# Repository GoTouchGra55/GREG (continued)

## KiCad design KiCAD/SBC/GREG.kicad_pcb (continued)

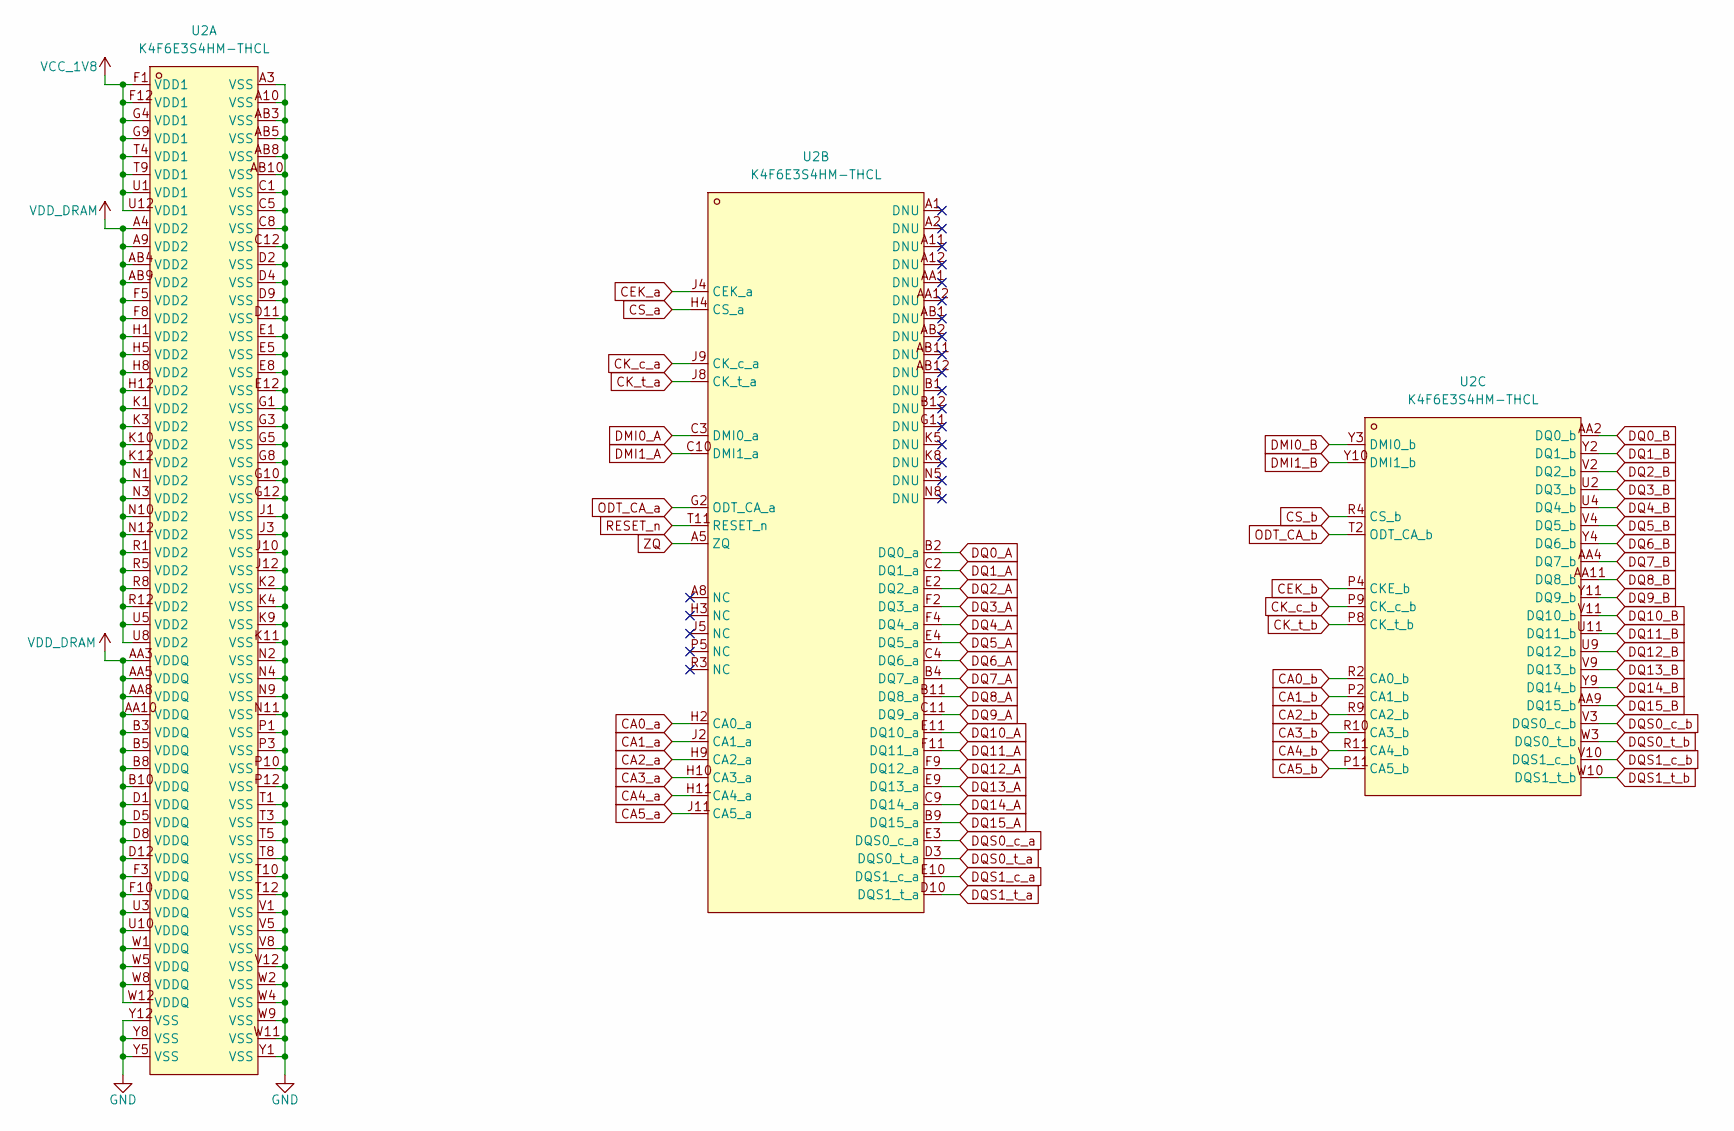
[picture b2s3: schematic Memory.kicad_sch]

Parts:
U2: K4F6E3S4HM-THCL; FBGA-200_L15.0-W10.0-BL_K4F6E3S4HM; MPN K4F6E3S4HM-THCL; LCSC Part C2920224

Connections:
CA0_a: U2.H2 (CA0_a); also elsewhere on the board
CA0_b: U2.R2 (CA0_b); also elsewhere on the board
CA1_a: U2.J2 (CA1_a); also elsewhere on the board
CA1_b: U2.P2 (CA1_b); also elsewhere on the board
CA2_a: U2.H9 (CA2_a); also elsewhere on the board
CA2_b: U2.R9 (CA2_b); also elsewhere on the board
CA3_a: U2.H10 (CA3_a); also elsewhere on the board
CA3_b: U2.R10 (CA3_b); also elsewhere on the board
CA4_a: U2.H11 (CA4_a); also elsewhere on the board
CA4_b: U2.R11 (CA4_b); also elsewhere on the board
CA5_a: U2.J11 (CA5_a); also elsewhere on the board
CA5_b: U2.P11 (CA5_b); also elsewhere on the board
CEK_a: U2.J4 (CEK_a), U2.P4 (CKE_b); also elsewhere on the board
CK_c_a: U2.J9 (CK_c_a), U2.P9 (CK_c_b); also elsewhere on the board
CK_t_a: U2.J8 (CK_t_a), U2.P8 (CK_t_b); also elsewhere on the board
CS_a: U2.H4 (CS_a); also elsewhere on the board
CS_b: U2.R4 (CS_b); also elsewhere on the board
DMI0_A: U2.C3 (DMI0_a); also elsewhere on the board
DMI0_B: U2.Y3 (DMI0_b); also elsewhere on the board
DMI1_A: U2.C10 (DMI1_a); also elsewhere on the board
DMI1_B: U2.Y10 (DMI1_b); also elsewhere on the board
DQ0_A: U2.B2 (DQ0_a); also elsewhere on the board
DQ0_B: U2.AA2 (DQ0_b); also elsewhere on the board
DQ1_A: U2.C2 (DQ1_a); also elsewhere on the board
DQ1_B: U2.Y2 (DQ1_b); also elsewhere on the board
DQ2_A: U2.E2 (DQ2_a); also elsewhere on the board
DQ2_B: U2.V2 (DQ2_b); also elsewhere on the board
DQ3_A: U2.F2 (DQ3_a); also elsewhere on the board
DQ3_B: U2.U2 (DQ3_b); also elsewhere on the board
DQ4_A: U2.F4 (DQ4_a); also elsewhere on the board
DQ4_B: U2.U4 (DQ4_b); also elsewhere on the board
DQ5_A: U2.E4 (DQ5_a); also elsewhere on the board
DQ5_B: U2.V4 (DQ5_b); also elsewhere on the board
DQ6_A: U2.C4 (DQ6_a); also elsewhere on the board
DQ6_B: U2.Y4 (DQ6_b); also elsewhere on the board
DQ7_A: U2.B4 (DQ7_a); also elsewhere on the board
DQ7_B: U2.AA4 (DQ7_b); also elsewhere on the board
DQ8_A: U2.B11 (DQ8_a); also elsewhere on the board
DQ8_B: U2.AA11 (DQ8_b); also elsewhere on the board
DQ9_A: U2.C11 (DQ9_a); also elsewhere on the board
DQ9_B: U2.Y11 (DQ9_b); also elsewhere on the board
DQ10_A: U2.E11 (DQ10_a); also elsewhere on the board
DQ10_B: U2.V11 (DQ10_b); also elsewhere on the board
DQ11_A: U2.F11 (DQ11_a); also elsewhere on the board
DQ11_B: U2.U11 (DQ11_b); also elsewhere on the board
DQ12_A: U2.F9 (DQ12_a); also elsewhere on the board
DQ12_B: U2.U9 (DQ12_b); also elsewhere on the board
DQ13_A: U2.E9 (DQ13_a); also elsewhere on the board
DQ13_B: U2.V9 (DQ13_b); also elsewhere on the board
DQ14_A: U2.C9 (DQ14_a); also elsewhere on the board
DQ14_B: U2.Y9 (DQ14_b); also elsewhere on the board
DQ15_A: U2.B9 (DQ15_a); also elsewhere on the board
DQ15_B: U2.AA9 (DQ15_b); also elsewhere on the board
DQS0_c_a: U2.E3 (DQS0_c_a); also elsewhere on the board
DQS0_c_b: U2.V3 (DQS0_c_b)
DQS0_t_a: U2.D3 (DQS0_t_a); also elsewhere on the board
DQS0_t_b: U2.W3 (DQS0_t_b)
DQS1_c_a: U2.E10 (DQS1_c_a); also elsewhere on the board
DQS1_c_b: U2.V10 (DQS1_c_b)
DQS1_t_a: U2.D10 (DQS1_t_a); also elsewhere on the board
DQS1_t_b: U2.W10 (DQS1_t_b)
GND: U2.A3 (VSS), U2.A10 (VSS), U2.AB3 (VSS), U2.AB5 (VSS), U2.AB8 (VSS), U2.AB10 (VSS), U2.C1 (VSS), U2.C5 (VSS), U2.C8 (VSS), U2.C12 (VSS), U2.D2 (VSS), U2.D4 (VSS), U2.D9 (VSS), U2.D11 (VSS), U2.E1 (VSS), U2.E5 (VSS), U2.E8 (VSS), U2.E12 (VSS), U2.G1 (VSS), U2.G3 (VSS), U2.G5 (VSS), U2.G8 (VSS), U2.G10 (VSS), U2.G12 (VSS), U2.J1 (VSS), U2.J3 (VSS), U2.J10 (VSS), U2.J12 (VSS), U2.K2 (VSS), U2.K4 (VSS), U2.K9 (VSS), U2.K11 (VSS), U2.N2 (VSS), U2.N4 (VSS), U2.N9 (VSS), U2.N11 (VSS), U2.P1 (VSS), U2.P3 (VSS), U2.P10 (VSS), U2.P12 (VSS), U2.T1 (VSS), U2.T3 (VSS), U2.T5 (VSS), U2.T8 (VSS), U2.T10 (VSS), U2.T12 (VSS), U2.V1 (VSS), U2.V5 (VSS), U2.V8 (VSS), U2.V12 (VSS), U2.W2 (VSS), U2.W4 (VSS), U2.W9 (VSS), U2.W11 (VSS), U2.Y1 (VSS), U2.Y5 (VSS), U2.Y8 (VSS), U2.Y12 (VSS); also elsewhere on the board
ODT_CA_a: U2.G2 (ODT_CA_a); also elsewhere on the board
ODT_CA_b: U2.T2 (ODT_CA_b); also elsewhere on the board
RESET_n: U2.T11 (RESET_n); also elsewhere on the board
VCC_1V8: U2.F1 (VDD1), U2.F12 (VDD1), U2.G4 (VDD1), U2.G9 (VDD1), U2.T4 (VDD1), U2.T9 (VDD1), U2.U1 (VDD1), U2.U12 (VDD1); also elsewhere on the board
VDD_DRAM: U2.A4 (VDD2), U2.A9 (VDD2), U2.AA3 (VDDQ), U2.AA5 (VDDQ), U2.AA8 (VDDQ), U2.AA10 (VDDQ), U2.AB4 (VDD2), U2.AB9 (VDD2), U2.B3 (VDDQ), U2.B5 (VDDQ), U2.B8 (VDDQ), U2.B10 (VDDQ), U2.D1 (VDDQ), U2.D5 (VDDQ), U2.D8 (VDDQ), U2.D12 (VDDQ), U2.F3 (VDDQ), U2.F5 (VDD2), U2.F8 (VDD2), U2.F10 (VDDQ), U2.H1 (VDD2), U2.H5 (VDD2), U2.H8 (VDD2), U2.H12 (VDD2), U2.K1 (VDD2), U2.K3 (VDD2), U2.K10 (VDD2), U2.K12 (VDD2), U2.N1 (VDD2), U2.N3 (VDD2), U2.N10 (VDD2), U2.N12 (VDD2), U2.R1 (VDD2), U2.R5 (VDD2), U2.R8 (VDD2), U2.R12 (VDD2), U2.U3 (VDDQ), U2.U5 (VDD2), U2.U8 (VDD2), U2.U10 (VDDQ), U2.W1 (VDDQ), U2.W5 (VDDQ), U2.W8 (VDDQ), U2.W12 (VDDQ); also elsewhere on the board
ZQ: U2.A5 (ZQ); also elsewhere on the board

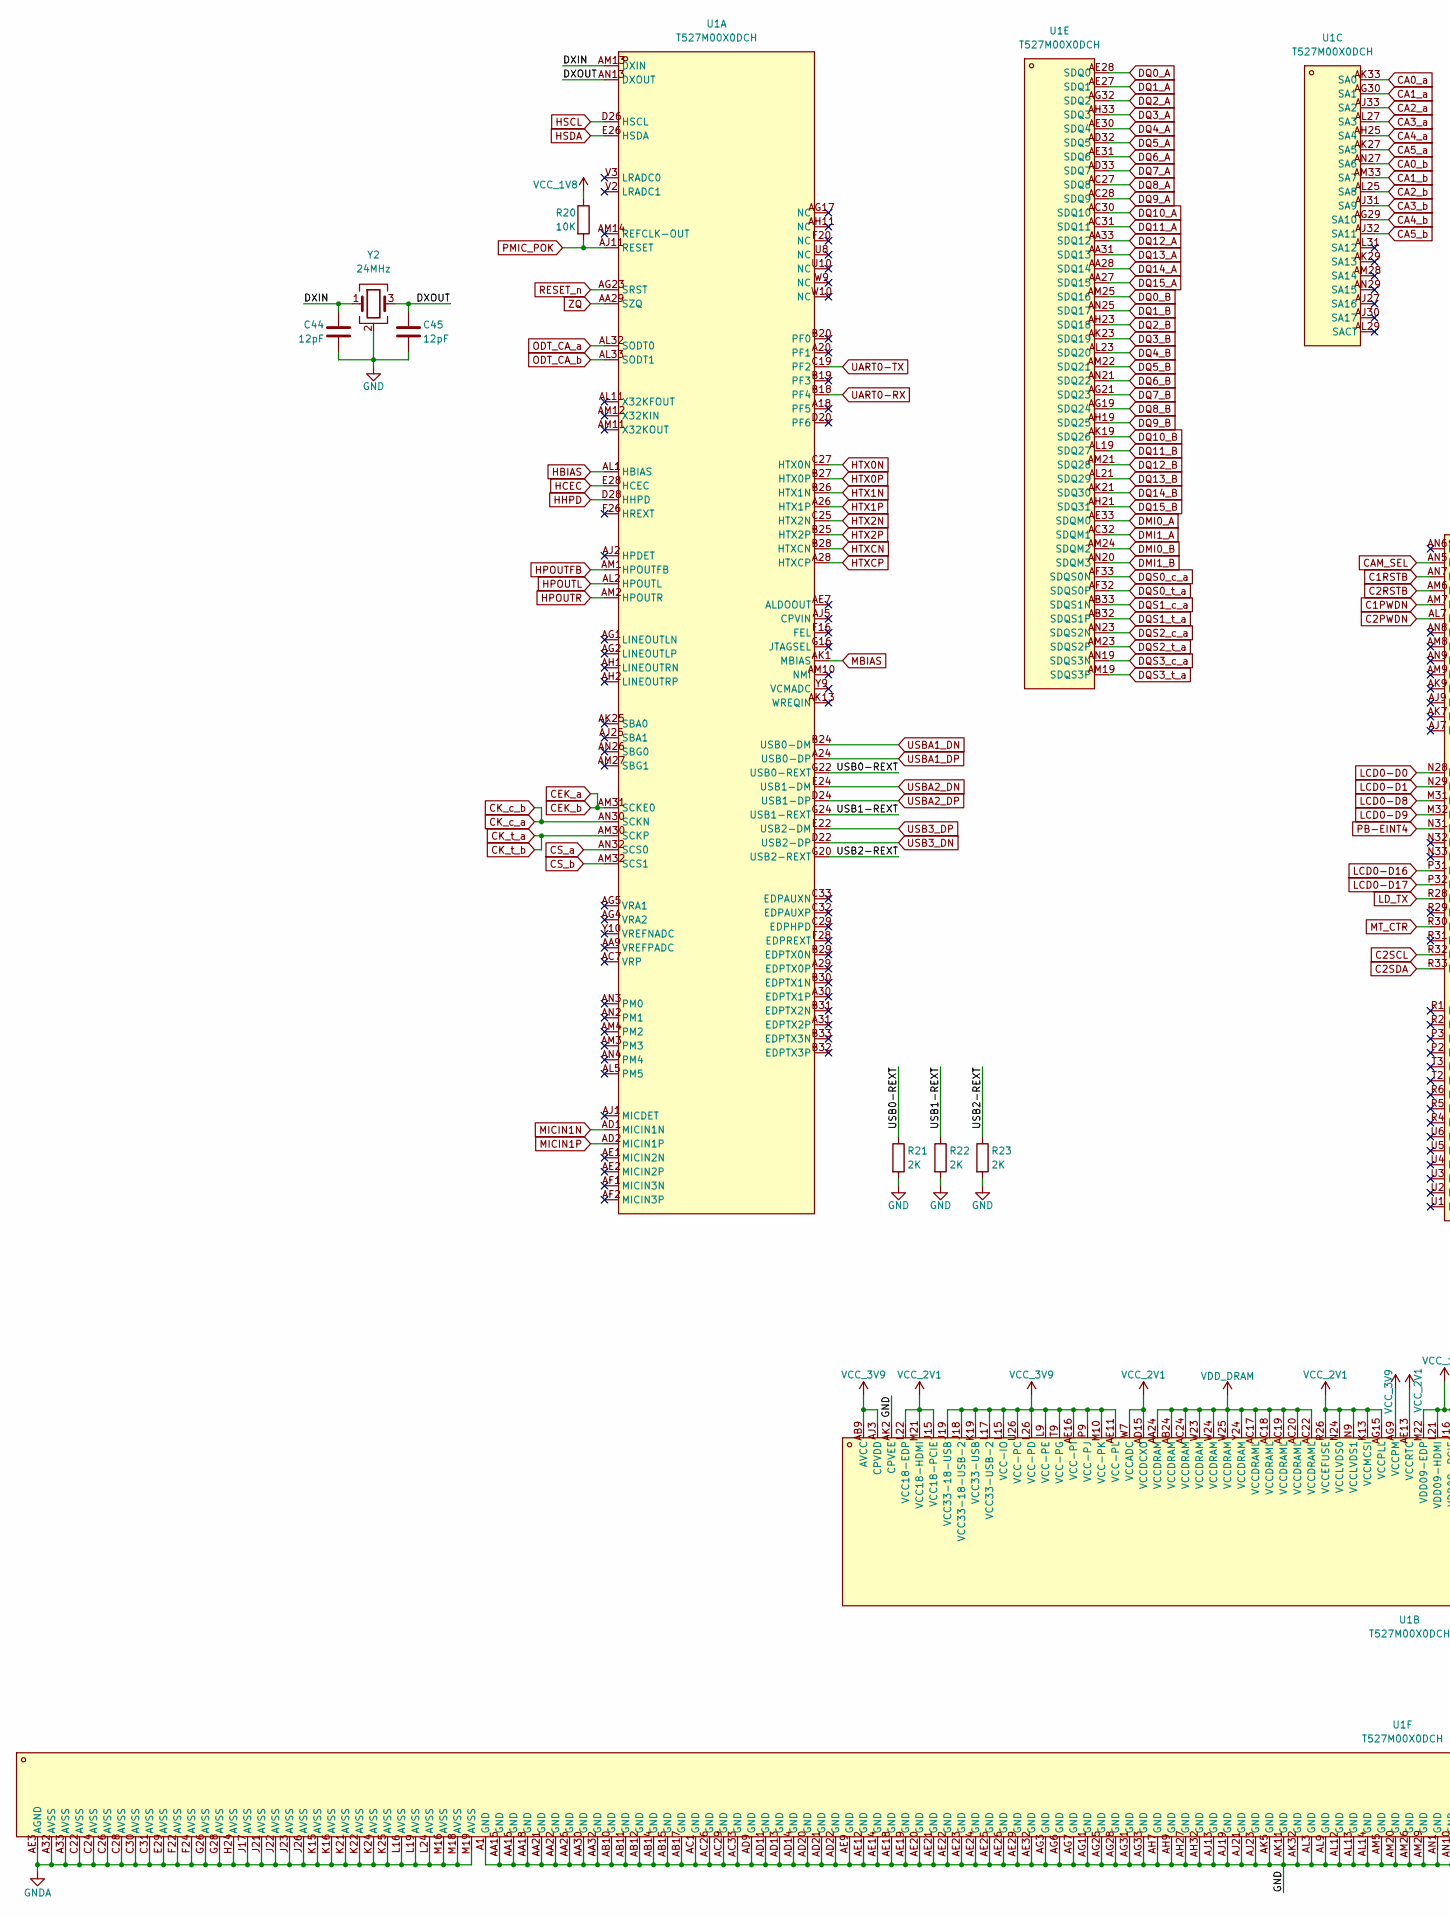
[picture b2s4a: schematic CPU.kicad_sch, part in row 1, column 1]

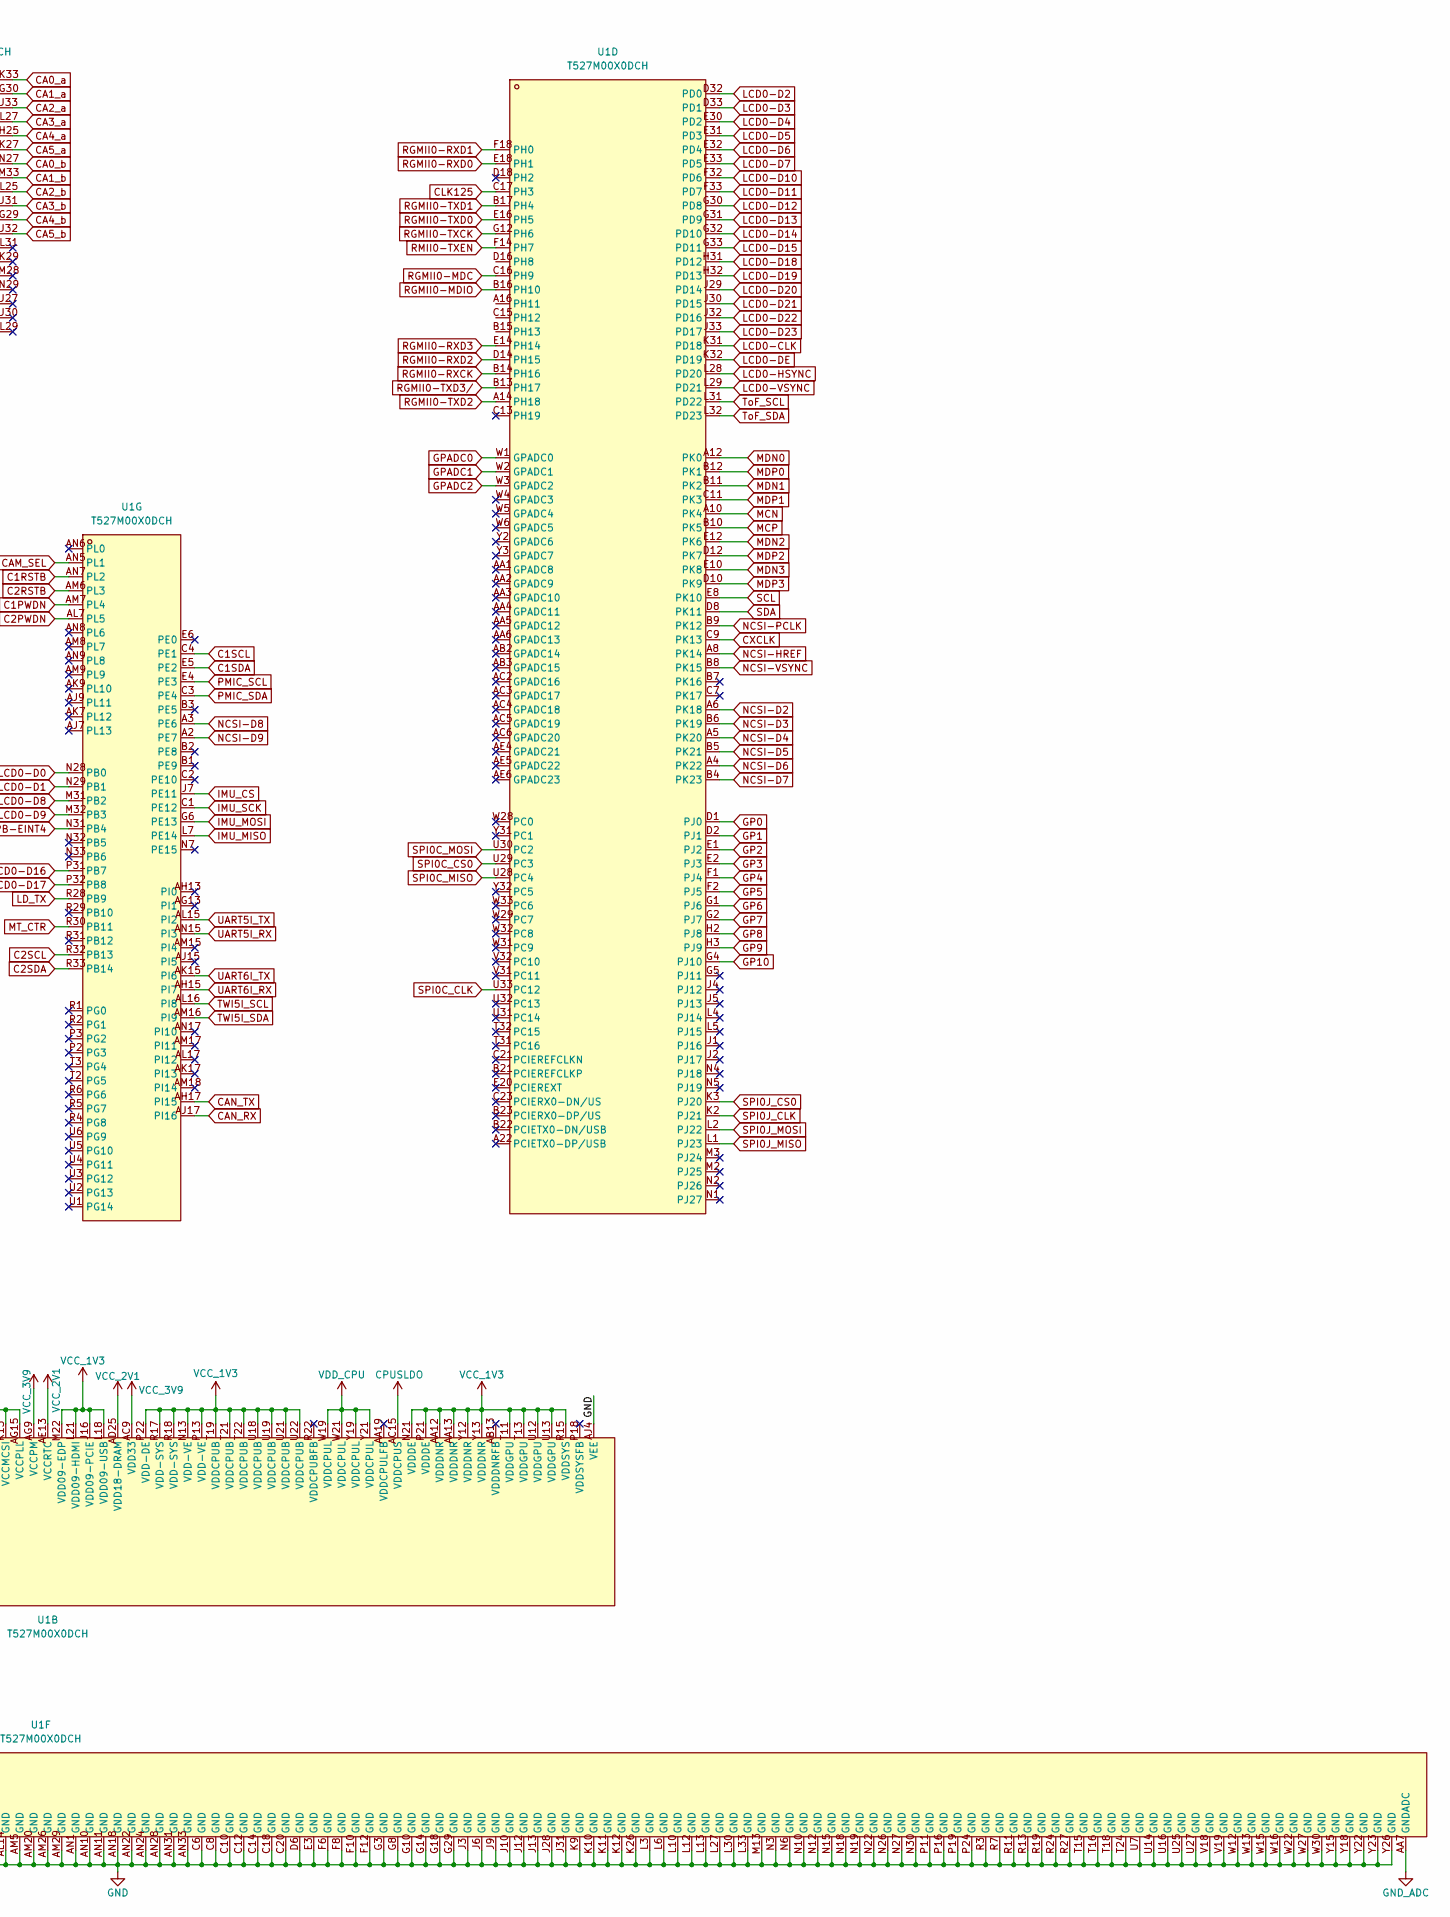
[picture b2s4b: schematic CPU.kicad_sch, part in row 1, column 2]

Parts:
C44, C45: 12pF; C_0402_1005Metric
R20: 10K; R_0402_1005Metric
R21, R22, R23: 2K; R_0402_1005Metric
U1: T527M00X0DCH; BGA-664_L17.0-W17.0_T527; MPN T527M00X0DCH; LCSC Part C28310420
Y2: 24MHz; Crystal_SMD_3225-4Pin_3.2x2.5mm

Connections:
/CPU/DXIN: C44.1, U1.AM13 (DXIN), Y2.1
/CPU/DXOUT: C45.1, U1.AN13 (DXOUT), Y2.3
/CPU/USB0-REXT: R21.1, U1.G22 (USB0-REXT)
/CPU/USB1-REXT: R22.1, U1.G24 (USB1-REXT)
/CPU/USB2-REXT: R23.1, U1.G20 (USB2-REXT)
C1PWDN: U1.AM7 (PL4); also elsewhere on the board
C1RSTB: U1.AN7 (PL2); also elsewhere on the board
C1SCL: U1.C4 (PE1); also elsewhere on the board
C1SDA: U1.E5 (PE2); also elsewhere on the board
C2PWDN: U1.AL7 (PL5); also elsewhere on the board
C2RSTB: U1.AM6 (PL3); also elsewhere on the board
C2SCL: U1.R32 (PB13); also elsewhere on the board
C2SDA: U1.R33 (PB14); also elsewhere on the board
CA0_a: U1.AK33 (SA0); also elsewhere on the board
CA0_b: U1.AN27 (SA6); also elsewhere on the board
CA1_a: U1.AG30 (SA1); also elsewhere on the board
CA1_b: U1.AM33 (SA7); also elsewhere on the board
CA2_a: U1.AJ33 (SA2); also elsewhere on the board
CA2_b: U1.AL25 (SA8); also elsewhere on the board
CA3_a: U1.AL27 (SA3); also elsewhere on the board
CA3_b: U1.AJ31 (SA9); also elsewhere on the board
CA4_a: U1.AH25 (SA4); also elsewhere on the board
CA4_b: U1.AG29 (SA10); also elsewhere on the board
CA5_a: U1.AK27 (SA5); also elsewhere on the board
CA5_b: U1.AJ32 (SA11); also elsewhere on the board
CAM_SEL: U1.AN5 (PL1); also elsewhere on the board
CAN_RX: U1.AJ17 (PI16); also elsewhere on the board
CAN_TX: U1.AH17 (PI15); also elsewhere on the board
CEK_a: U1.AM31 (SCKE0); also elsewhere on the board
CK_c_a: U1.AN30 (SCKN); also elsewhere on the board
CK_t_a: U1.AM30 (SCKP); also elsewhere on the board
CLK125: U1.C17 (PH3); also elsewhere on the board
CPUSLDO: U1.AC15 (VDDCPUS); also elsewhere on the board
CS_a: U1.AN32 (SCS0); also elsewhere on the board
CS_b: U1.AM32 (SCS1); also elsewhere on the board
CXCLK: U1.C9 (PK13); also elsewhere on the board
DMI0_A: U1.AE33 (SDQM0); also elsewhere on the board
DMI0_B: U1.AM24 (SDQM2); also elsewhere on the board
DMI1_A: U1.AC32 (SDQM1); also elsewhere on the board
DMI1_B: U1.AN20 (SDQM3); also elsewhere on the board
DQ0_A: U1.AE28 (SDQ0); also elsewhere on the board
DQ0_B: U1.AM25 (SDQ16); also elsewhere on the board
DQ1_A: U1.AE27 (SDQ1); also elsewhere on the board
DQ1_B: U1.AN25 (SDQ17); also elsewhere on the board
DQ2_A: U1.AG32 (SDQ2); also elsewhere on the board
DQ2_B: U1.AH23 (SDQ18); also elsewhere on the board
DQ3_A: U1.AH33 (SDQ3); also elsewhere on the board
DQ3_B: U1.AK23 (SDQ19); also elsewhere on the board
DQ4_A: U1.AE30 (SDQ4); also elsewhere on the board
DQ4_B: U1.AL23 (SDQ20); also elsewhere on the board
DQ5_A: U1.AD32 (SDQ5); also elsewhere on the board
DQ5_B: U1.AM22 (SDQ21); also elsewhere on the board
DQ6_A: U1.AE31 (SDQ6); also elsewhere on the board
DQ6_B: U1.AN21 (SDQ22); also elsewhere on the board
DQ7_A: U1.AD33 (SDQ7); also elsewhere on the board
DQ7_B: U1.AG21 (SDQ23); also elsewhere on the board
DQ8_A: U1.AC27 (SDQ8); also elsewhere on the board
DQ8_B: U1.AG19 (SDQ24); also elsewhere on the board
DQ9_A: U1.AC28 (SDQ9); also elsewhere on the board
DQ9_B: U1.AH19 (SDQ25); also elsewhere on the board
DQ10_A: U1.AC30 (SDQ10); also elsewhere on the board
DQ10_B: U1.AK19 (SDQ26); also elsewhere on the board
DQ11_A: U1.AC31 (SDQ11); also elsewhere on the board
DQ11_B: U1.AL19 (SDQ27); also elsewhere on the board
DQ12_A: U1.AA33 (SDQ12); also elsewhere on the board
DQ12_B: U1.AM21 (SDQ28); also elsewhere on the board
DQ13_A: U1.AA31 (SDQ13); also elsewhere on the board
DQ13_B: U1.AL21 (SDQ29); also elsewhere on the board
DQ14_A: U1.AA28 (SDQ14); also elsewhere on the board
DQ14_B: U1.AK21 (SDQ30); also elsewhere on the board
DQ15_A: U1.AA27 (SDQ15); also elsewhere on the board
DQ15_B: U1.AH21 (SDQ31); also elsewhere on the board
DQS0_c_a: U1.AF33 (SDQS0N); also elsewhere on the board
DQS0_t_a: U1.AF32 (SDQS0P); also elsewhere on the board
DQS1_c_a: U1.AB33 (SDQS1N); also elsewhere on the board
DQS1_t_a: U1.AB32 (SDQS1P); also elsewhere on the board
DQS2_c_a: U1.AN23 (SDQS2N)
DQS2_t_a: U1.AM23 (SDQS2P)
DQS3_c_a: U1.AN19 (SDQS3N)
DQS3_t_a: U1.AM19 (SDQS3P)
GND: C44.2, C45.2, R21.2, R22.2, R23.2, U1.A1 (GND), U1.AA15 (GND), U1.AA16 (GND), U1.AA18 (GND), U1.AA21 (GND), U1.AA22 (GND), U1.AA26 (GND), U1.AA30 (GND), U1.AA32 (GND), U1.AB10 (GND), U1.AB11 (GND), U1.AB12 (GND), U1.AB14 (GND), U1.AB15 (GND), U1.AB17 (GND), U1.AC1 (GND), U1.AC26 (GND), U1.AC29 (GND), U1.AC33 (GND), U1.AD9 (GND), U1.AD11 (GND), U1.AD13 (GND), U1.AD14 (GND), U1.AD20 (GND), U1.AD21 (GND), U1.AD22 (GND), U1.AE9 (GND), U1.AE12 (GND), U1.AE14 (GND), U1.AE18 (GND), U1.AE19 (GND), U1.AE20 (GND), U1.AE21 (GND), U1.AE22 (GND), U1.AE23 (GND), U1.AE24 (GND), U1.AE25 (GND), U1.AE26 (GND), U1.AE29 (GND), U1.AE32 (GND), U1.AG3 (GND), U1.AG6 (GND), U1.AG7 (GND), U1.AG11 (GND), U1.AG25 (GND), U1.AG28 (GND), U1.AG31 (GND), U1.AG33 (GND), U1.AH7 (GND), U1.AH9 (GND), U1.AH27 (GND), U1.AH32 (GND), U1.AJ4 (VEE), U1.AJ13 (GND), U1.AJ19 (GND), U1.AJ21 (GND), U1.AJ23 (GND), U1.AK2 (CPVEE), U1.AK5 (GND), U1.AK11 (GND), U1.AK32 (GND), U1.AL3 (GND), U1.AL9 (GND), U1.AL12 (GND), U1.AL13 (GND), U1.AL14 (GND), U1.AM5 (GND), U1.AM20 (GND), U1.AM26 (GND), U1.AM29 (GND), U1.AN1 (GND), U1.AN10 (GND), U1.AN11 (GND), U1.AN18 (GND), U1.AN22 (GND), U1.AN24 (GND), U1.AN28 (GND), U1.AN31 (GND), U1.AN33 (GND), U1.C6 (GND), U1.C8 (GND), U1.C10 (GND), U1.C12 (GND), U1.C14 (GND), U1.C18 (GND), U1.C20 (GND), U1.D6 (GND), U1.E3 (GND), U1.F6 (GND), U1.F8 (GND), U1.F10 (GND), U1.F12 (GND), U1.G3 (GND), U1.G8 (GND), U1.G10 (GND), U1.G14 (GND), U1.G18 (GND), U1.G29 (GND), U1.J3 (GND), U1.J6 (GND), U1.J9 (GND), U1.J10 (GND), U1.J12 (GND), U1.J13 (GND), U1.J28 (GND), U1.J31 (GND), U1.K9 (GND), U1.K10 (GND), U1.K11 (GND), U1.K12 (GND), U1.K26 (GND), U1.L3 (GND), U1.L6 (GND), U1.L10 (GND), U1.L12 (GND), U1.L13 (GND), U1.L27 (GND), U1.L30 (GND), U1.L33 (GND), U1.M13 (GND), U1.N3 (GND), U1.N6 (GND), U1.N10 (GND), U1.N12 (GND), U1.N15 (GND), U1.N18 (GND), U1.N19 (GND), U1.N22 (GND), U1.N26 (GND), U1.N27 (GND), U1.N30 (GND), U1.P11 (GND), U1.P16 (GND), U1.P19 (GND), U1.P24 (GND), U1.R3 (GND), U1.R7 (GND), U1.R11 (GND), U1.R13 (GND), U1.R19 (GND), U1.R24 (GND), U1.R27 (GND), U1.T15 (GND), U1.T16 (GND), U1.T18 (GND), U1.T24 (GND), U1.U7 (GND), U1.U14 (GND), U1.U16 (GND), U1.U25 (GND), U1.U27 (GND), U1.V18 (GND), U1.V19 (GND), U1.W12 (GND), U1.W13 (GND), U1.W15 (GND), U1.W16 (GND), U1.W22 (GND), U1.W27 (GND), U1.W30 (GND), U1.Y15 (GND), U1.Y18 (GND), U1.Y22 (GND), U1.Y23 (GND), U1.Y26 (GND), Y2.2 (G), Y2.4 (G); also elsewhere on the board
GNDA: U1.A32 (AVSS), U1.A33 (AVSS), U1.AE3 (AGND), U1.C22 (AVSS), U1.C24 (AVSS), U1.C26 (AVSS), U1.C28 (AVSS), U1.C30 (AVSS), U1.C31 (AVSS), U1.E29 (AVSS), U1.F22 (AVSS), U1.F24 (AVSS), U1.G26 (AVSS), U1.G28 (AVSS), U1.H24 (AVSS), U1.J17 (AVSS), U1.J21 (AVSS), U1.J22 (AVSS), U1.J23 (AVSS), U1.J26 (AVSS), U1.K15 (AVSS), U1.K16 (AVSS), U1.K21 (AVSS), U1.K22 (AVSS), U1.K24 (AVSS), U1.K25 (AVSS), U1.L16 (AVSS), U1.L19 (AVSS), U1.L24 (AVSS), U1.M16 (AVSS), U1.M18 (AVSS), U1.M19 (AVSS)
GND_ADC: U1.AA7 (GNDADC)
GP0: U1.D1 (PJ0); also elsewhere on the board
GP1: U1.D2 (PJ1); also elsewhere on the board
GP2: U1.E1 (PJ2); also elsewhere on the board
GP3: U1.E2 (PJ3); also elsewhere on the board
GP4: U1.F1 (PJ4); also elsewhere on the board
GP5: U1.F2 (PJ5); also elsewhere on the board
GP6: U1.G1 (PJ6); also elsewhere on the board
GP7: U1.G2 (PJ7); also elsewhere on the board
GP8: U1.H2 (PJ8); also elsewhere on the board
GP9: U1.H3 (PJ9); also elsewhere on the board
GP10: U1.G4 (PJ10); also elsewhere on the board
GPADC0: U1.W1 (GPADC0); also elsewhere on the board
GPADC1: U1.W2 (GPADC1); also elsewhere on the board
GPADC2: U1.W3 (GPADC2); also elsewhere on the board
HBIAS: U1.AL1 (HBIAS)
HCEC: U1.E28 (HCEC); also elsewhere on the board
HHPD: U1.D28 (HHPD); also elsewhere on the board
HPOUTFB: U1.AM1 (HPOUTFB); also elsewhere on the board
HPOUTL: U1.AL2 (HPOUTL); also elsewhere on the board
HPOUTR: U1.AM2 (HPOUTR); also elsewhere on the board
HSCL: U1.D26 (HSCL); also elsewhere on the board
HSDA: U1.E26 (HSDA); also elsewhere on the board
HTX0N: U1.C27 (HTX0N); also elsewhere on the board
HTX0P: U1.B27 (HTX0P); also elsewhere on the board
HTX1N: U1.B26 (HTX1N); also elsewhere on the board
HTX1P: U1.A26 (HTX1P); also elsewhere on the board
HTX2N: U1.C25 (HTX2N); also elsewhere on the board
HTX2P: U1.B25 (HTX2P); also elsewhere on the board
HTXCN: U1.B28 (HTXCN); also elsewhere on the board
HTXCP: U1.A28 (HTXCP); also elsewhere on the board
IMU_CS: U1.J7 (PE11); also elsewhere on the board
IMU_MISO: U1.L7 (PE14); also elsewhere on the board
IMU_MOSI: U1.G6 (PE13); also elsewhere on the board
IMU_SCK: U1.C1 (PE12); also elsewhere on the board
LCD0-CLK: U1.K31 (PD18); also elsewhere on the board
LCD0-D0: U1.N28 (PB0); also elsewhere on the board
LCD0-D1: U1.N29 (PB1); also elsewhere on the board
LCD0-D2: U1.D32 (PD0); also elsewhere on the board
LCD0-D3: U1.D33 (PD1); also elsewhere on the board
LCD0-D4: U1.E30 (PD2); also elsewhere on the board
LCD0-D5: U1.E31 (PD3); also elsewhere on the board
LCD0-D6: U1.E32 (PD4); also elsewhere on the board
LCD0-D7: U1.E33 (PD5); also elsewhere on the board
LCD0-D8: U1.M31 (PB2); also elsewhere on the board
LCD0-D9: U1.M32 (PB3); also elsewhere on the board
LCD0-D10: U1.F32 (PD6); also elsewhere on the board
LCD0-D11: U1.F33 (PD7); also elsewhere on the board
LCD0-D12: U1.G30 (PD8); also elsewhere on the board
LCD0-D13: U1.G31 (PD9); also elsewhere on the board
LCD0-D14: U1.G32 (PD10); also elsewhere on the board
LCD0-D15: U1.G33 (PD11); also elsewhere on the board
LCD0-D16: U1.P31 (PB7); also elsewhere on the board
LCD0-D17: U1.P32 (PB8); also elsewhere on the board
LCD0-D18: U1.H31 (PD12); also elsewhere on the board
LCD0-D19: U1.H32 (PD13); also elsewhere on the board
LCD0-D20: U1.J29 (PD14); also elsewhere on the board
LCD0-D21: U1.J30 (PD15); also elsewhere on the board
LCD0-D22: U1.J32 (PD16); also elsewhere on the board
LCD0-D23: U1.J33 (PD17); also elsewhere on the board
LCD0-DE: U1.K32 (PD19); also elsewhere on the board
LCD0-HSYNC: U1.L28 (PD20); also elsewhere on the board
LCD0-VSYNC: U1.L29 (PD21); also elsewhere on the board
LD_TX: U1.R28 (PB9); also elsewhere on the board
MBIAS: U1.AK1 (MBIAS); also elsewhere on the board
MCN: U1.A10 (PK4)
MCP: U1.B10 (PK5)
MDN0: U1.A12 (PK0)
MDN1: U1.B11 (PK2)
MDN2: U1.E12 (PK6)
MDN3: U1.E10 (PK8)
MDP0: U1.B12 (PK1)
MDP1: U1.C11 (PK3)
MDP2: U1.D12 (PK7)
MDP3: U1.D10 (PK9)
MICIN1N: U1.AD1 (MICIN1N); also elsewhere on the board
MICIN1P: U1.AD2 (MICIN1P); also elsewhere on the board
MT_CTR: U1.R30 (PB11); also elsewhere on the board
NCSI-D2: U1.A6 (PK18); also elsewhere on the board
NCSI-D3: U1.B6 (PK19); also elsewhere on the board
NCSI-D4: U1.A5 (PK20); also elsewhere on the board
NCSI-D5: U1.B5 (PK21); also elsewhere on the board
NCSI-D6: U1.A4 (PK22); also elsewhere on the board
NCSI-D7: U1.B4 (PK23); also elsewhere on the board
NCSI-D8: U1.A3 (PE6); also elsewhere on the board
NCSI-D9: U1.A2 (PE7); also elsewhere on the board
NCSI-HREF: U1.A8 (PK14); also elsewhere on the board
NCSI-PCLK: U1.B9 (PK12); also elsewhere on the board
NCSI-VSYNC: U1.B8 (PK15); also elsewhere on the board
ODT_CA_a: U1.AL32 (SODT0); also elsewhere on the board
ODT_CA_b: U1.AL33 (SODT1); also elsewhere on the board
PB-EINT4: U1.N31 (PB4); also elsewhere on the board
PMIC_POK: R20.2, U1.AJ11 (RESET); also elsewhere on the board
PMIC_SCL: U1.E4 (PE3); also elsewhere on the board
PMIC_SDA: U1.C3 (PE4); also elsewhere on the board
RESET_n: U1.AG23 (SRST); also elsewhere on the board
RGMII0-MDC: U1.C16 (PH9); also elsewhere on the board
RGMII0-MDIO: U1.B16 (PH10); also elsewhere on the board
RGMII0-RXCK: U1.B14 (PH16); also elsewhere on the board
RGMII0-RXD0: U1.E18 (PH1); also elsewhere on the board
RGMII0-RXD1: U1.F18 (PH0); also elsewhere on the board
RGMII0-RXD2: U1.D14 (PH15); also elsewhere on the board
RGMII0-RXD3: U1.E14 (PH14); also elsewhere on the board
RGMII0-TXCK: U1.G12 (PH6); also elsewhere on the board
RGMII0-TXD0: U1.E16 (PH5); also elsewhere on the board
RGMII0-TXD1: U1.B17 (PH4); also elsewhere on the board
RGMII0-TXD2: U1.A14 (PH18); also elsewhere on the board
RGMII0-TXD3/: U1.B13 (PH17)
RMII0-TXEN: U1.F14 (PH7); also elsewhere on the board
SCL: U1.E8 (PK10)
SDA: U1.D8 (PK11)
SPI0C_CLK: U1.U33 (PC12); also elsewhere on the board
SPI0C_CS0: U1.U29 (PC3); also elsewhere on the board
SPI0C_MISO: U1.U28 (PC4); also elsewhere on the board
SPI0C_MOSI: U1.U30 (PC2); also elsewhere on the board
SPI0J_CLK: U1.K2 (PJ21); also elsewhere on the board
SPI0J_CS0: U1.K3 (PJ20); also elsewhere on the board
SPI0J_MISO: U1.L1 (PJ23); also elsewhere on the board
SPI0J_MOSI: U1.L2 (PJ22); also elsewhere on the board
TWI5I_SCL: U1.AL16 (PI8); also elsewhere on the board
TWI5I_SDA: U1.AM16 (PI9); also elsewhere on the board
ToF_SCL: U1.L31 (PD22); also elsewhere on the board
ToF_SDA: U1.L32 (PD23); also elsewhere on the board
UART0-RX: U1.B18 (PF4); also elsewhere on the board
UART0-TX: U1.C19 (PF2); also elsewhere on the board
UART5I_RX: U1.AN15 (PI3); also elsewhere on the board
UART5I_TX: U1.AL15 (PI2); also elsewhere on the board
UART6I_RX: U1.AH15 (PI7); also elsewhere on the board
UART6I_TX: U1.AK15 (PI6); also elsewhere on the board
USB3_DN: U1.D22 (USB2-DP); also elsewhere on the board
USB3_DP: U1.E22 (USB2-DM); also elsewhere on the board
USBA1_DN: U1.B24 (USB0-DM); also elsewhere on the board
USBA1_DP: U1.A24 (USB0-DP); also elsewhere on the board
USBA2_DN: U1.E24 (USB1-DM); also elsewhere on the board
USBA2_DP: U1.D24 (USB1-DP); also elsewhere on the board
VCC_1V3: U1.AA12 (VDDDNR), U1.AA13 (VDDDNR), U1.J16 (VDD09-PCIE), U1.L18 (VDD09-USB), U1.L21 (VDD09-HDMI), U1.M22 (VDD09-EDP), U1.N13 (VDD-VE), U1.N21 (VDDDE), U1.P13 (VDD-VE), U1.P21 (VDDDE), U1.P22 (VDD-DE), U1.R15 (VDDSYS), U1.R17 (VDD-SYS), U1.R18 (VDD-SYS), U1.T11 (VDDGPU), U1.T13 (VDDGPU), U1.T19 (VDDCPUB), U1.T21 (VDDCPUB), U1.T22 (VDDCPUB), U1.U12 (VDDGPU), U1.U13 (VDDGPU), U1.U18 (VDDCPUB), U1.U19 (VDDCPUB), U1.U21 (VDDCPUB), U1.U22 (VDDCPUB), U1.Y12 (VDDDNR), U1.Y13 (VDDDNR); also elsewhere on the board
VCC_1V8: R20.1; also elsewhere on the board
VCC_2V1: U1.AD15 (VCCDCXO), U1.AD25 (VDD18-DRAM), U1.AE13 (VCCRTC), U1.AG15 (VCCPLL), U1.J15 (VCC18-PCIE), U1.K13 (VCCMCSI), U1.L22 (VCC18-EDP), U1.M21 (VCC18-HDMI), U1.N9 (VCCLVDS1), U1.N24 (VCCLVDS0), U1.R26 (VCCEFUSE), U1.W7 (VCCADC); also elsewhere on the board
VCC_3V9: U1.AB9 (AVCC), U1.AC9 (VDD33), U1.AE11 (VCC-PL), U1.AE16 (VCC-PI), U1.AG9 (VCCPM), U1.AJ3 (CPVDD), U1.J18 (VCC33-18-USB-2), U1.J19 (VCC33-18-USB), U1.K19 (VCC33-USB), U1.L9 (VCC-PE), U1.L15 (VCC-IO), U1.L17 (VCC33-USB-2), U1.L26 (VCC-PD), U1.M10 (VCC-PK), U1.P9 (VCC-PJ), U1.T9 (VCC-PG), U1.U26 (VCC-PC); also elsewhere on the board
VDD_CPU: U1.W19 (VDDCPUL), U1.W21 (VDDCPUL), U1.Y19 (VDDCPUL), U1.Y21 (VDDCPUL); also elsewhere on the board
VDD_DRAM: U1.AA24 (VCCDRAM), U1.AB24 (VCCDRAM), U1.AC17 (VCCDRAML), U1.AC18 (VCCDRAML), U1.AC19 (VCCDRAML), U1.AC20 (VCCDRAML), U1.AC22 (VCCDRAML), U1.AC24 (VCCDRAM), U1.W23 (VCCDRAM), U1.W24 (VCCDRAM), U1.W25 (VCCDRAM), U1.Y24 (VCCDRAM); also elsewhere on the board
ZQ: U1.AA29 (SZQ); also elsewhere on the board

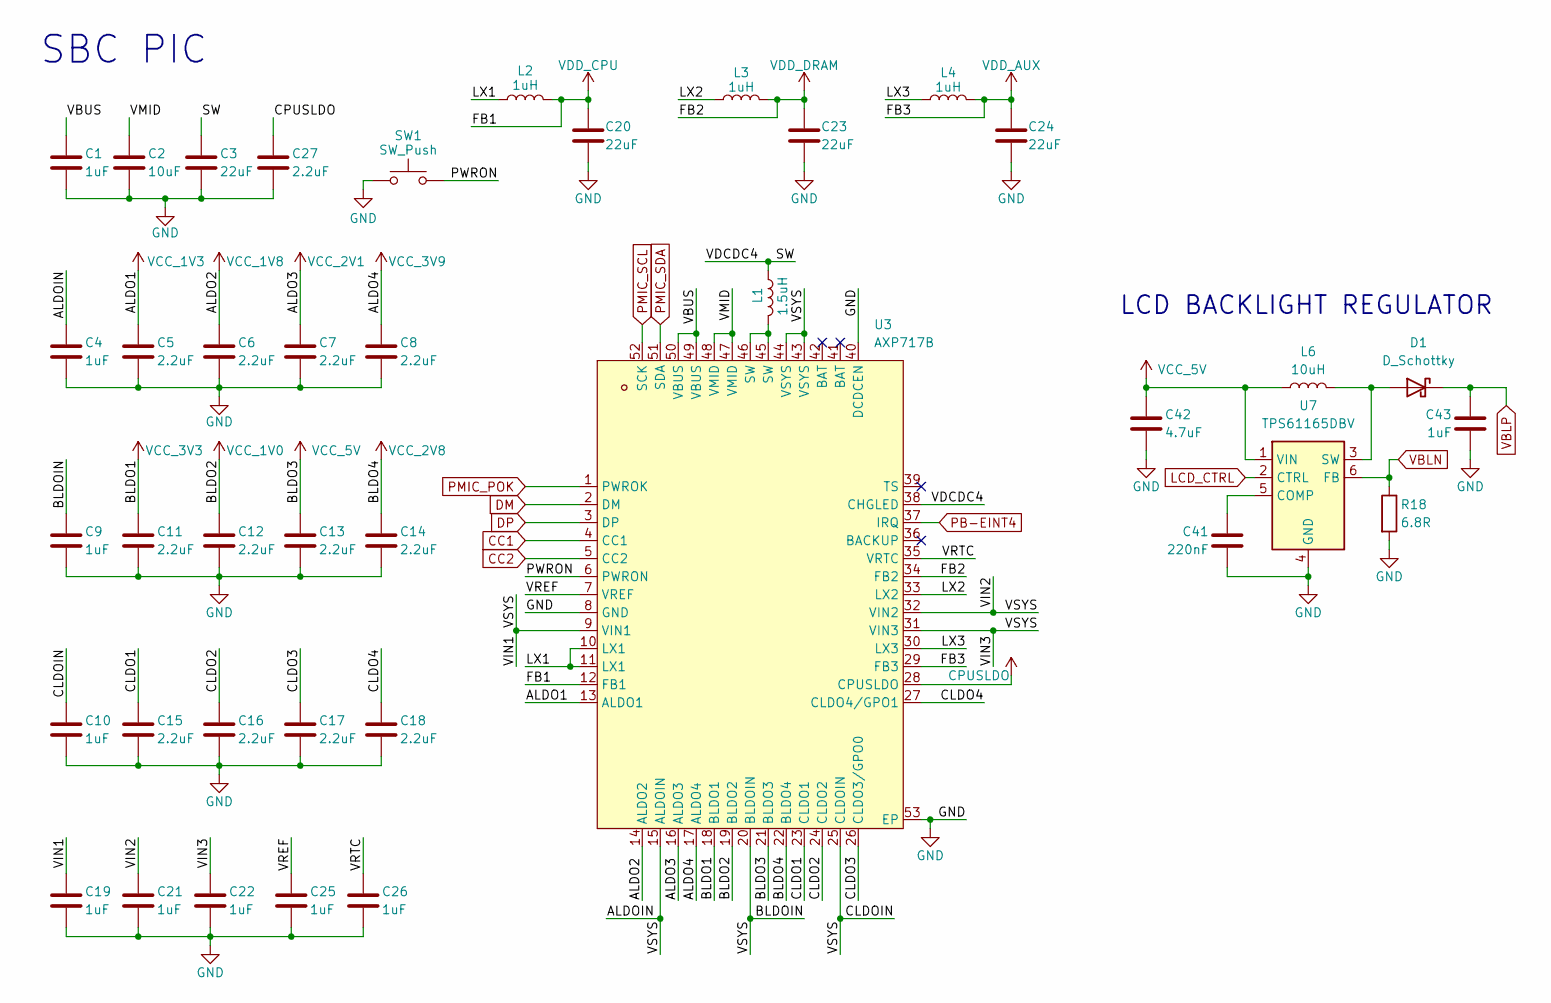
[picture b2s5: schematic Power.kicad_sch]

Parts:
C1, C4, C9, C10, C19, C21, C22, C25, C26, C43: 1uF; C_0805_2012Metric
C2: 10uF; C_0805_2012Metric
C3, C20, C23, C24: 22uF; C_0805_2012Metric
C5, C6, C7, C8, C11, C12, C13, C14, C15, C16, C17, C18, C27: 2.2uF; C_0805_2012Metric
C41: 220nF; C_0402_1005Metric
C42: 4.7uF; C_0805_2012Metric
D1: D_Schottky; D_SOD-123
L1: 1.5uH; L_Cenker_CKCS3015
L2, L3, L4: 1uH; L_Cenker_CKCS3015
L6: 10uH; L_Cenker_CKCS3012
R18: 6.8R; R_0402_1005Metric
SW1: SW_Push; SW_Push_SPST_NO_Alps_SKRK
U3: AXP717B; QFN-52_L6.0-W6.0-P0.40-TL-EP4.5; MPN AXP717B; LCSC Part C45360051
U7: TPS61165DBV; SOT-23-6

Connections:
/Power/ALDOIN: C4.1, C9.1, C10.1, C19.1, C21.1, C22.1, U3.9 (VIN1), U3.15 (ALDOIN), U3.20 (BLDOIN), U3.25 (CLDOIN), U3.31 (VIN3), U3.32 (VIN2), U3.43 (VSYS), U3.44 (VSYS)
/Power/CLDO1: C15.1, U3.23 (CLDO1)
/Power/CLDO2: C16.1, U3.24 (CLDO2)
/Power/CLDO3: C17.1, U3.26 (CLDO3/GPO0)
/Power/CLDO4: C18.1, U3.27 (CLDO4/GPO1)
/Power/LX1: L2.1, U3.10 (LX1), U3.11 (LX1)
/Power/LX2: L3.1, U3.33 (LX2)
/Power/LX3: L4.1, U3.30 (LX3)
/Power/PWRON: SW1.1, U3.6 (PWRON)
/Power/SW: C3.1, L1.1, U3.38 (CHGLED)
/Power/VBUS: C1.1, U3.49 (VBUS), U3.50 (VBUS)
/Power/VMID: C2.1, U3.47 (VMID), U3.48 (VMID)
/Power/VREF: C25.1, U3.7 (VREF)
/Power/VRTC: C26.1, U3.35 (VRTC)
CC1: U3.4 (CC1)
CC2: U3.5 (CC2)
CPUSLDO: C27.1, U3.28 (CPUSLDO); also elsewhere on the board
DM: U3.2 (DM)
DP: U3.3 (DP)
GND: C1.2, C2.2, C3.2, C4.2, C5.2, C6.2, C7.2, C8.2, C9.2, C10.2, C11.2, C12.2, C13.2, C14.2, C15.2, C16.2, C17.2, C18.2, C19.2, C20.2, C21.2, C22.2, C23.2, C24.2, C25.2, C26.2, C27.2, C41.2, C42.2, C43.2, R18.2, SW1.2, U3.8 (GND), U3.40 (DCDCEN), U3.53 (EP), U7.4 (GND); also elsewhere on the board
LCD_CTRL: U7.2 (CTRL)
unnamed: D1.2 (A), L6.2, U7.3 (SW)
unnamed: L1.2, U3.45 (SW), U3.46 (SW)
unnamed: C41.1, U7.5 (COMP)
PB-EINT4: U3.37 (IRQ); also elsewhere on the board
PMIC_POK: U3.1 (PWROK); also elsewhere on the board
PMIC_SCL: U3.52 (SCK); also elsewhere on the board
PMIC_SDA: U3.51 (SDA); also elsewhere on the board
VBLN: R18.1, U7.6 (FB); also elsewhere on the board
VBLP: C43.1, D1.1 (K); also elsewhere on the board
VCC_1V0: C12.1, U3.19 (BLDO2); also elsewhere on the board
VCC_1V3: C5.1, U3.13 (ALDO1); also elsewhere on the board
VCC_1V8: C6.1, U3.14 (ALDO2); also elsewhere on the board
VCC_2V1: C7.1, U3.16 (ALDO3); also elsewhere on the board
VCC_2V8: C14.1, U3.22 (BLDO4); also elsewhere on the board
VCC_3V3: C11.1, U3.18 (BLDO1); also elsewhere on the board
VCC_3V9: C8.1, U3.17 (ALDO4); also elsewhere on the board
VCC_5V: C13.1, C42.1, L6.1, U3.21 (BLDO3), U7.1 (VIN); also elsewhere on the board
VDD_AUX: C24.1, L4.2, U3.29 (FB3)
VDD_CPU: C20.1, L2.2, U3.12 (FB1); also elsewhere on the board
VDD_DRAM: C23.1, L3.2, U3.34 (FB2); also elsewhere on the board

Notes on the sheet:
SBC PIC
LCD BACKLIGHT REGULATOR
